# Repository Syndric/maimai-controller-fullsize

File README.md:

# Maimai Controller Fullsize

A fullsize homemade maimai machine.
Current guide can be found at [this google doc](https://docs.google.com/document/d/1rlUKWXb57IGA04_7nuOs167HQMNG2UHoSkpQwI1rv1U/edit?usp=sharing).
This guide is not finished yet, but most of the files you need to make the machine are here. READ CAREFULLY!

# Disclaimers

Read [Romper's fullsize guide](https://github.com/ir0nq/maimai-homemade-controller) before reading the instructions here.
DO NOT LASERCUT WITH THE ITO TEMPLATE AS IS. I'm not sure if the traces are wide enough. It's only good to be used for hand tracing/cut.
DO NOT MAKE THE CART IN MY DESIGN. It's not really stable.

I am NOT financially responsible for any mishaps you might have. This is only a guide. Double check all measurements.

# License

CC-NC, feel free to modify the project but don't make any money from this guide.

# Bill of Materials
Not complete

## PCB

- Raspberry Pi Nano
- USB C Connector
- 5.1k ohm resistor 0603
- 1uF capacitor 0603
- MPR121 Modules
- Dupont Pin headers
- JST XH 3 Pin connectors, headers
- 50m red wire
- 20m yellow wire
- 20m black wire
- SN74LV1T34DBVR Level shifter
- WS2812B RGB LED
- Mai pico IO PCB x1
- Syndric's RGB PCB x8

## Main Build

- Rabbit buttons
- ITO Film 40ohm 1m
- 43" TV
- 24" side-to-side Octagon glass
- Chair leg floor protectors
- 2020 48" Aluminum
- Small wood screws for buttons
- Wood screws for mai spacers
- Appropriate spacers

# Tools Needed

- Flathead screwdriver
- Philips screwdriver
- 3D printer
- Router
- Miter saw
- PPE

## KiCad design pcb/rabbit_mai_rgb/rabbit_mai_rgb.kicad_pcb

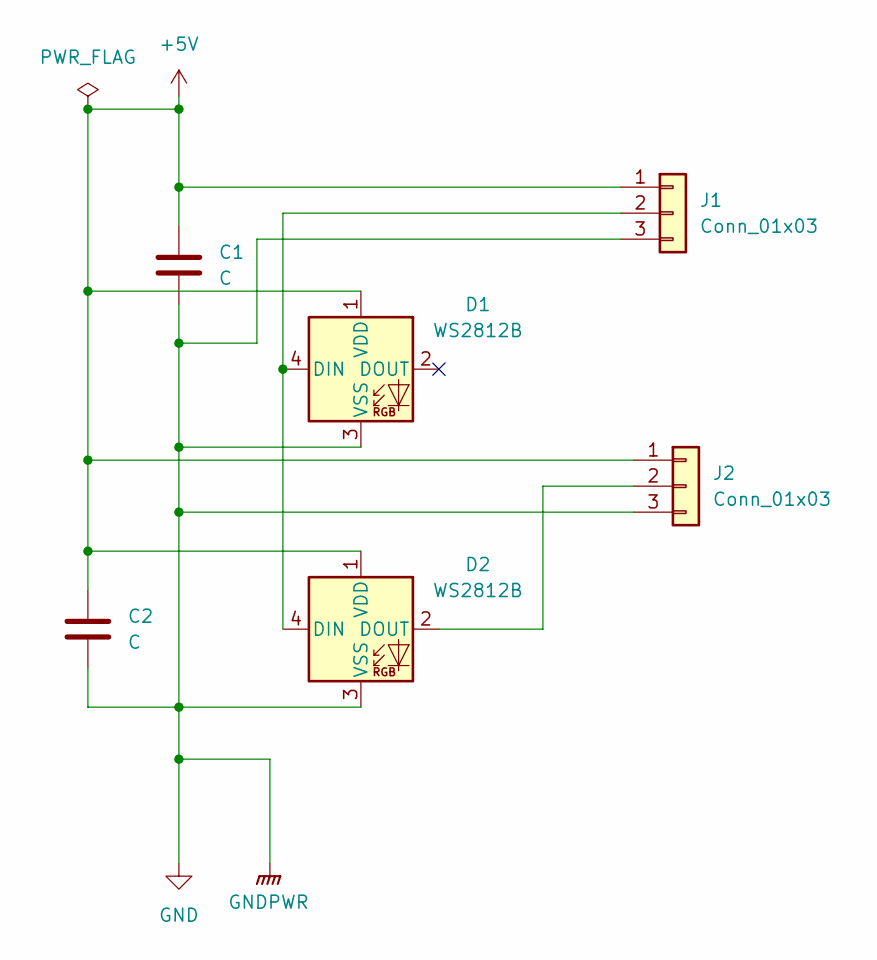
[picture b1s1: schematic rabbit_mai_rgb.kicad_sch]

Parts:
C1, C2: C; C_0603_1608Metric_Pad1.08x0.95mm_HandSolder
D1, D2: WS2812B; LED_WS2812B_PLCC4_5.0x5.0mm_P3.2mm
J1, J2: Conn_01x03; JST_XH_S3B-XH-A_1x03_P2.50mm_Horizontal

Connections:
+5V: C1.1, C2.1, D1.1 (VDD), D2.1 (VDD), J1.1, J2.1
GND: C1.2, C2.2, D1.3 (VSS), D2.3 (VSS), J1.3, J2.3
unnamed: D1.4 (DIN), D2.4 (DIN), J1.2
unnamed: D2.2 (DOUT), J2.2

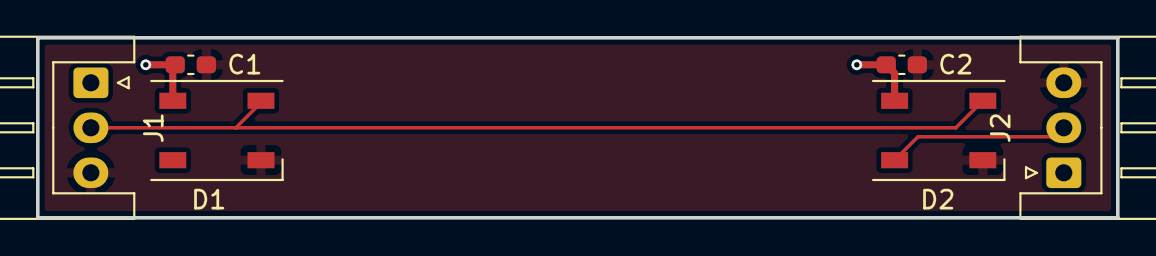
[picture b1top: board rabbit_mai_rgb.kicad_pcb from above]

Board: 2 copper layers, 60.0 x 10.0 mm, 6 parts (0 on the bottom side), 4 nets.

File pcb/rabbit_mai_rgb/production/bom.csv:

Designator,Footprint,Quantity,Value,LCSC Part #
"C1, C2",0603,2,C,
"D1, D2",LED_WS2812B_PLCC4_5.0x5.0mm_P3.2mm,2,WS2812B,
"J1, J2",JST_XH_S3B-XH-A_1x03_P2.50mm_Horizontal,2,Conn_01x03,

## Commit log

2024-10-21 add button cad
2024-11-05 add maispacer
2025-01-25 add: basic files
2025-01-25 add pics
